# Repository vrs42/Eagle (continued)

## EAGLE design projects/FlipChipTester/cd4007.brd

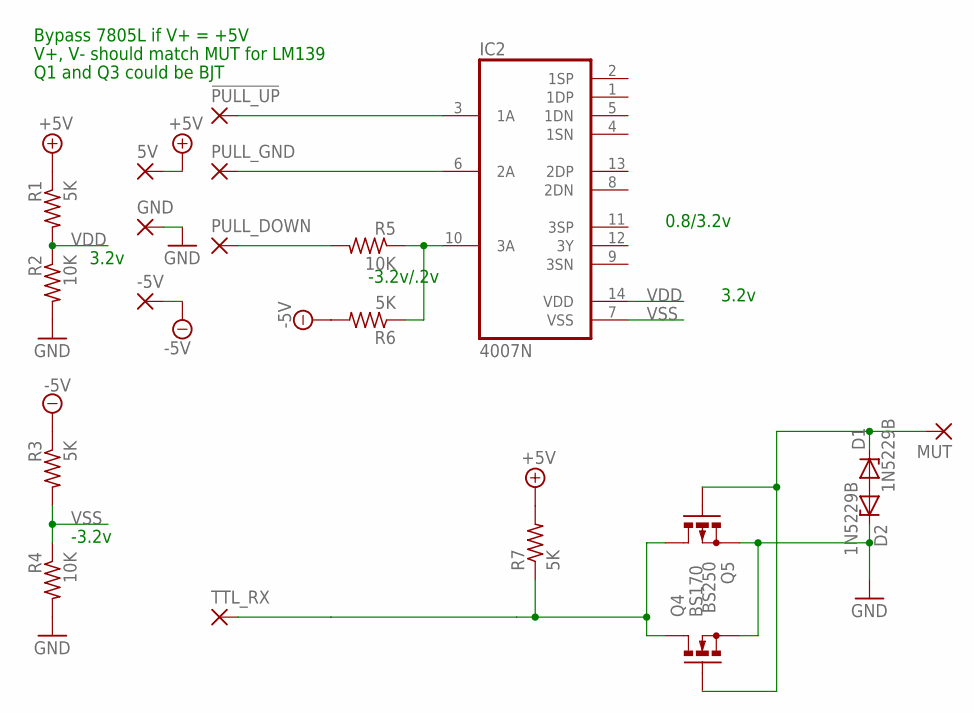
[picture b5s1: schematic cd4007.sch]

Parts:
5V: 1,6/0,9
!PULL_UP: 1,6/0,9
-5V: 1,6/0,9
D1, D2: 1N5229B; DO35Z10
GND: 1,6/0,9
IC2: 4007N; DIL14
MUT: 1,6/0,9
PULL_DOWN: 1,6/0,9
PULL_GND: 1,6/0,9
Q4: BS170; SOT54E
Q5: BS250; SOT54E
R1, R3, R6, R7: 5K; 0207/10
R2, R4, R5: 10K; 0207/10
TTL_RX: 1,6/0,9

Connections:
+5V: 5V.1, R1.1, R7.2
-5V: -5V.1, R3.1, R6.2
GND: D2.C, GND.1, Q4.S, Q5.S, R2.2, R4.2
unnamed: D1.C, MUT.1, Q4.G, Q5.G
unnamed: IC2.10 (3A), R5.1, R6.1
unnamed: IC2.6 (2A), PULL_GND.1
unnamed: PULL_DOWN.1, R5.2
unnamed: D1.A, D2.A
unnamed: Q4.D, Q5.D, R7.1, TTL_RX.1
unnamed: !PULL_UP.1, IC2.3 (1A)
VDD: IC2.14 (VDD), R1.2, R2.1
VSS: IC2.7 (VSS), R3.2, R4.1

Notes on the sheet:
V+, V- should match MUT for LM139
Bypass 7805L if V+ = +5V
-3.2v
-3.2v/.2v
3.2v
0.8/3.2v
Q1 and Q3 could be BJT

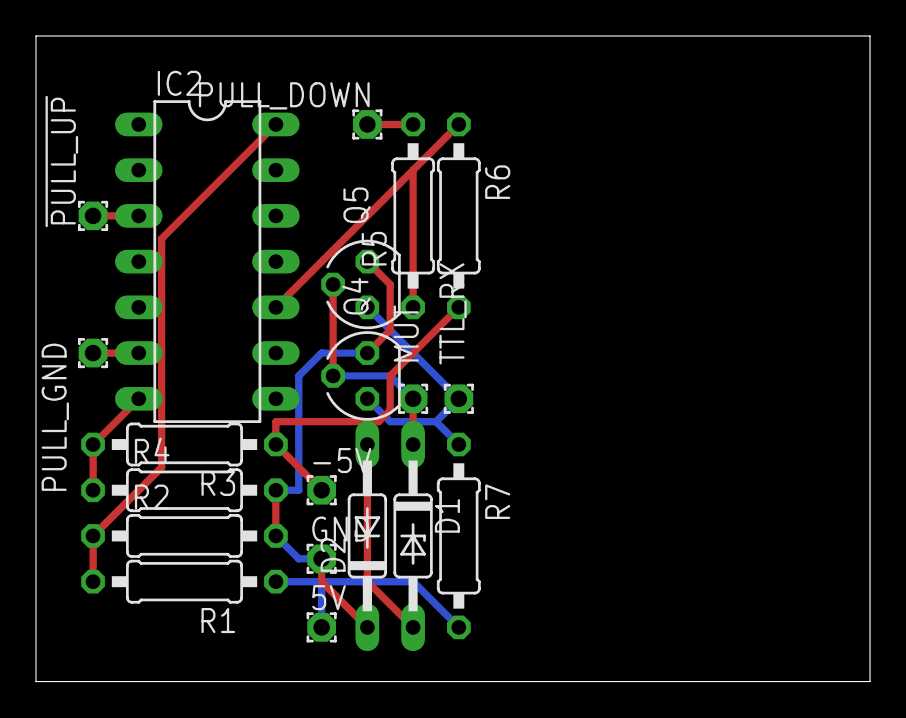
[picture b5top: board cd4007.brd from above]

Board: 2 copper layers, 46.3 x 35.9 mm, 20 parts (0 on the bottom side), 12 nets.

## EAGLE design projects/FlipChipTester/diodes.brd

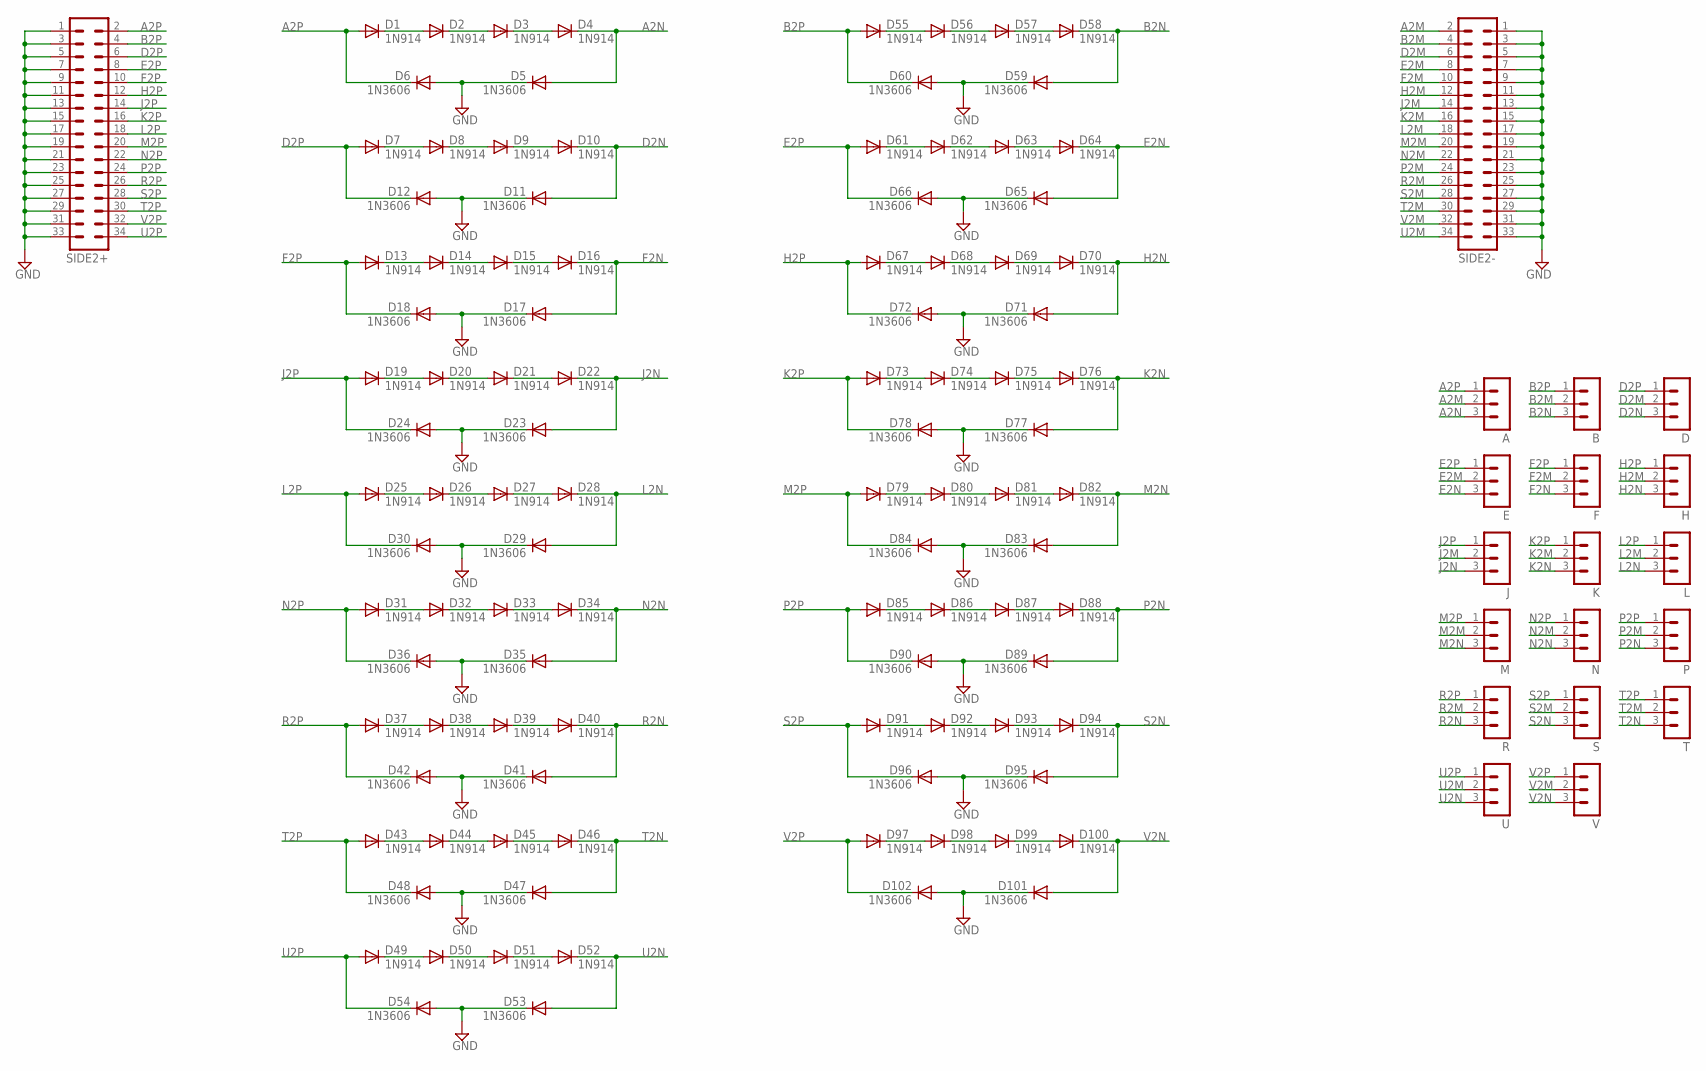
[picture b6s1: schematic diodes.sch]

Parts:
A: MA03-1
B: MA03-1
D: MA03-1
D1, D2, D3, D4, D7, D8, D9, D10, D13, D14, D15, D16, D19, D20, D21, D22, D25, D26, D27, D28, D31, D32, D33, D34, D37, D38, D39, D40, D43, D44, D45, D46, D49, D50, D51, D52, D55, D56, D57, D58, D61, D62, D63, D64, D67, D68, D69, D70, D73, D74, D75, D76, D79, D80, D81, D82, D85, D86, D87, D88, D91, D92, D93, D94, D97, D98, D99, D100: 1N914; DO35-10
D5, D6, D11, D12, D17, D18, D23, D24, D29, D30, D35, D36, D41, D42, D47, D48, D53, D54, D59, D60, D65, D66, D71, D72, D77, D78, D83, D84, D89, D90, D95, D96, D101, D102: 1N3606; DO35-10
E: MA03-1
F: MA03-1
H: MA03-1
J: MA03-1
K: MA03-1
L: MA03-1
M: MA03-1
N: MA03-1
P: MA03-1
R: MA03-1
S: MA03-1
SIDE2+, SIDE2-: MA17-2
T: MA03-1
U: MA03-1
V: MA03-1

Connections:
A2M: A.2, SIDE2-.2
A2N: A.3, D4.C, D5.A
A2P: A.1, D1.A, D6.C, SIDE2+.2
B2M: B.2, SIDE2-.4
B2N: B.3, D58.C, D59.A
B2P: B.1, D55.A, D60.C, SIDE2+.4
D2M: D.2, SIDE2-.6
D2N: D.3, D10.C, D11.A
D2P: D.1, D7.A, D12.C, SIDE2+.6
E2M: E.2, SIDE2-.8
E2N: D64.C, D65.A, E.3
E2P: D61.A, D66.C, E.1, SIDE2+.8
F2M: F.2, SIDE2-.10
F2N: D16.C, D17.A, F.3
F2P: D13.A, D18.C, F.1, SIDE2+.10
GND: D5.C, D6.A, D11.C, D12.A, D17.C, D18.A, D23.C, D24.A, D29.C, D30.A, D35.C, D36.A, D41.C, D42.A, D47.C, D48.A, D53.C, D54.A, D59.C, D60.A, D65.C, D66.A, D71.C, D72.A, D77.C, D78.A, D83.C, D84.A, D89.C, D90.A, D95.C, D96.A, D101.C, D102.A, SIDE2+.1, SIDE2+.3, SIDE2+.5, SIDE2+.7, SIDE2+.9, SIDE2+.11, SIDE2+.13, SIDE2+.15, SIDE2+.17, SIDE2+.19, SIDE2+.21, SIDE2+.23, SIDE2+.25, SIDE2+.27, SIDE2+.29, SIDE2+.31, SIDE2+.33, SIDE2-.1, SIDE2-.3, SIDE2-.5, SIDE2-.7, SIDE2-.9, SIDE2-.11, SIDE2-.13, SIDE2-.15, SIDE2-.17, SIDE2-.19, SIDE2-.21, SIDE2-.23, SIDE2-.25, SIDE2-.27, SIDE2-.29, SIDE2-.31, SIDE2-.33
H2M: H.2, SIDE2-.12
H2N: D70.C, D71.A, H.3
H2P: D67.A, D72.C, H.1, SIDE2+.12
J2M: J.2, SIDE2-.14
J2N: D22.C, D23.A, J.3
J2P: D19.A, D24.C, J.1, SIDE2+.14
K2M: K.2, SIDE2-.16
K2N: D76.C, D77.A, K.3
K2P: D73.A, D78.C, K.1, SIDE2+.16
L2M: L.2, SIDE2-.18
L2N: D28.C, D29.A, L.3
L2P: D25.A, D30.C, L.1, SIDE2+.18
M2M: M.2, SIDE2-.20
M2N: D82.C, D83.A, M.3
M2P: D79.A, D84.C, M.1, SIDE2+.20
N2M: N.2, SIDE2-.22
N2N: D34.C, D35.A, N.3
N2P: D31.A, D36.C, N.1, SIDE2+.22
unnamed: D1.C, D2.A
unnamed: D2.C, D3.A
unnamed: D3.C, D4.A
unnamed: D7.C, D8.A
unnamed: D8.C, D9.A
unnamed: D9.C, D10.A
unnamed: D13.C, D14.A
unnamed: D14.C, D15.A
unnamed: D15.C, D16.A
unnamed: D19.C, D20.A
unnamed: D20.C, D21.A
unnamed: D21.C, D22.A
unnamed: D25.C, D26.A
unnamed: D26.C, D27.A
unnamed: D27.C, D28.A
unnamed: D31.C, D32.A
unnamed: D32.C, D33.A
unnamed: D33.C, D34.A
unnamed: D37.C, D38.A
unnamed: D38.C, D39.A
unnamed: D39.C, D40.A
unnamed: D43.C, D44.A
unnamed: D44.C, D45.A
unnamed: D45.C, D46.A
unnamed: D49.C, D50.A
unnamed: D50.C, D51.A
unnamed: D51.C, D52.A
unnamed: D55.C, D56.A
unnamed: D56.C, D57.A
unnamed: D57.C, D58.A
unnamed: D61.C, D62.A
unnamed: D62.C, D63.A
unnamed: D63.C, D64.A
unnamed: D67.C, D68.A
unnamed: D68.C, D69.A
unnamed: D69.C, D70.A
unnamed: D73.C, D74.A
unnamed: D74.C, D75.A
unnamed: D75.C, D76.A
unnamed: D79.C, D80.A
unnamed: D80.C, D81.A
unnamed: D81.C, D82.A
unnamed: D85.C, D86.A
unnamed: D86.C, D87.A
unnamed: D87.C, D88.A
unnamed: D91.C, D92.A
unnamed: D92.C, D93.A
unnamed: D93.C, D94.A
unnamed: D97.C, D98.A
unnamed: D98.C, D99.A
unnamed: D99.C, D100.A
P2M: P.2, SIDE2-.24
P2N: D88.C, D89.A, P.3
P2P: D85.A, D90.C, P.1, SIDE2+.24
R2M: R.2, SIDE2-.26
R2N: D40.C, D41.A, R.3
R2P: D37.A, D42.C, R.1, SIDE2+.26
S2M: S.2, SIDE2-.28
S2N: D94.C, D95.A, S.3
S2P: D91.A, D96.C, S.1, SIDE2+.28
T2M: SIDE2-.30, T.2
T2N: D46.C, D47.A, T.3
T2P: D43.A, D48.C, SIDE2+.30, T.1
U2M: SIDE2-.34, U.2
U2N: D52.C, D53.A, U.3
U2P: D49.A, D54.C, SIDE2+.34, U.1
V2M: SIDE2-.32, V.2
V2N: D100.C, D101.A, V.3
V2P: D97.A, D102.C, SIDE2+.32, V.1

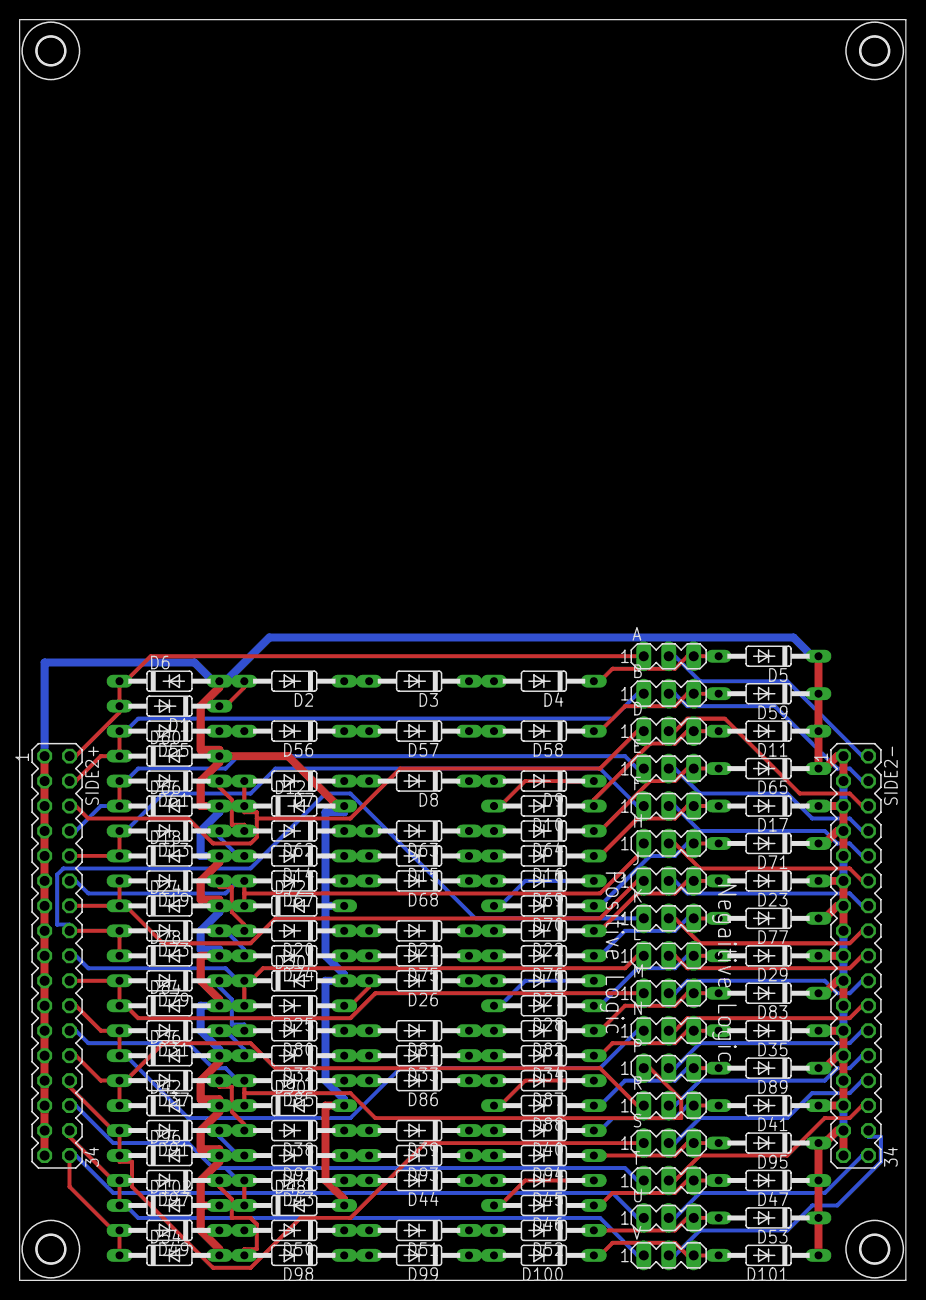
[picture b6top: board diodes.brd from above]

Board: 2 copper layers, 90.2 x 128.3 mm, 125 parts (0 on the bottom side), 103 nets.

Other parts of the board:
U$1, U$2, U$3, U$4: 2,8

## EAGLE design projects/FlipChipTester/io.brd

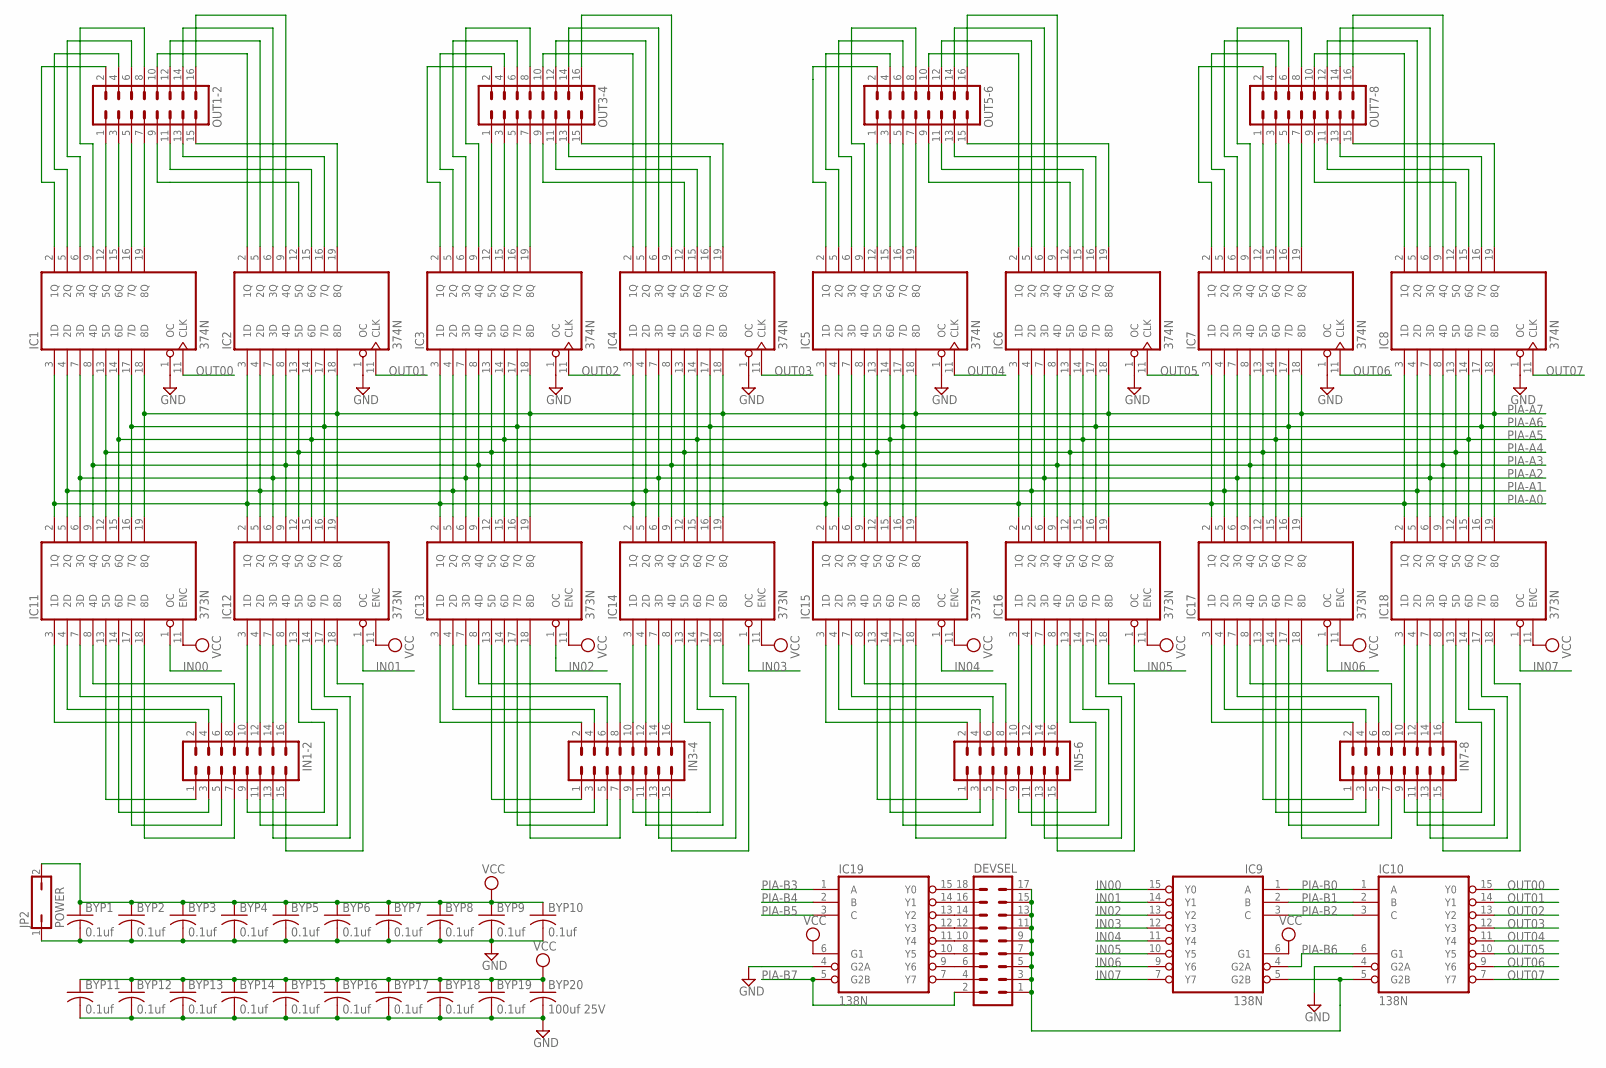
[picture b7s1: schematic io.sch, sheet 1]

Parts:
BYP1, BYP2, BYP3, BYP4, BYP5, BYP6, BYP7, BYP8, BYP9, BYP10, BYP11, BYP12, BYP13, BYP14, BYP15, BYP16, BYP17, BYP18, BYP19: 0.1uf; C050-025X075
BYP20: 100uf 25V; C150-064X183
DEVSEL: MA09-2
IC1, IC2, IC3, IC4, IC5, IC6, IC7, IC8: 374N; DIL20
IC9, IC10, IC19: 138N; DIL16
IC11, IC12, IC13, IC14, IC15, IC16, IC17, IC18: 373N; DIL20
IN1-2, IN3-4, IN5-6, IN7-8: MA08-2
JP2: POWER; JP1
OUT1-2, OUT3-4, OUT5-6, OUT7-8: MA08-2

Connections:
GND: BYP1.2, BYP2.2, BYP3.2, BYP4.2, BYP5.2, BYP6.2, BYP7.2, BYP8.2, BYP9.2, BYP10.2, BYP11.2, BYP12.2, BYP13.2, BYP14.2, BYP15.2, BYP16.2, BYP17.2, BYP18.2, BYP19.2, BYP20.2, IC1.1 (OC), IC1.10 (GND), IC2.1 (OC), IC2.10 (GND), IC3.1 (OC), IC3.10 (GND), IC4.1 (OC), IC4.10 (GND), IC5.1 (OC), IC5.10 (GND), IC6.1 (OC), IC6.10 (GND), IC7.1 (OC), IC7.10 (GND), IC8.1 (OC), IC8.10 (GND), IC9.8 (GND), IC10.4 (G2A), IC10.8 (GND), IC11.10 (GND), IC12.10 (GND), IC13.10 (GND), IC14.10 (GND), IC15.10 (GND), IC16.10 (GND), IC17.10 (GND), IC18.10 (GND), IC19.4 (G2A), IC19.8 (GND), JP2.1; also elsewhere on the board
IN00: IC9.15 (Y0), IC11.1 (OC)
IN01: IC9.14 (Y1), IC12.1 (OC)
IN02: IC9.13 (Y2), IC13.1 (OC)
IN03: IC9.12 (Y3), IC14.1 (OC)
IN04: IC9.11 (Y4), IC15.1 (OC)
IN05: IC9.10 (Y5), IC16.1 (OC)
IN06: IC9.9 (Y6), IC17.1 (OC)
IN07: IC9.7 (Y7), IC18.1 (OC)
unnamed: IC12.3 (1D), IN1-2.10
unnamed: IC12.4 (2D), IN1-2.12
unnamed: DEVSEL.18, IC19.15 (Y0)
unnamed: DEVSEL.16, IC19.14 (Y1)
unnamed: DEVSEL.14, IC19.13 (Y2)
unnamed: DEVSEL.12, IC19.12 (Y3)
unnamed: IC12.7 (3D), IN1-2.14
unnamed: IC12.8 (4D), IN1-2.16
unnamed: IC11.8 (4D), IN1-2.8
unnamed: IC11.7 (3D), IN1-2.6
unnamed: IC11.4 (2D), IN1-2.4
unnamed: IC11.3 (1D), IN1-2.2
unnamed: IC11.13 (5D), IN1-2.1
unnamed: IC11.14 (6D), IN1-2.3
unnamed: IC11.17 (7D), IN1-2.5
unnamed: IC11.18 (8D), IN1-2.7
unnamed: IC12.13 (5D), IN1-2.9
unnamed: IC12.14 (6D), IN1-2.11
unnamed: IC12.17 (7D), IN1-2.13
unnamed: IC12.18 (8D), IN1-2.15
unnamed: DEVSEL.10, IC19.11 (Y4)
unnamed: DEVSEL.8, IC19.10 (Y5)
unnamed: DEVSEL.6, IC19.9 (Y6)
unnamed: DEVSEL.4, IC19.7 (Y7)
unnamed: DEVSEL.1, DEVSEL.3, DEVSEL.5, DEVSEL.7, DEVSEL.9, DEVSEL.11, DEVSEL.13, DEVSEL.15, DEVSEL.17, IC9.5 (G2B), IC10.5 (G2B)
unnamed: IC5.2 (1Q), OUT5-6.2
unnamed: IC18.8 (4D), IN7-8.16
unnamed: IC18.3 (1D), IN7-8.10
unnamed: IC14.3 (1D), IN3-4.10
unnamed: IC14.4 (2D), IN3-4.12
unnamed: IC14.7 (3D), IN3-4.14
unnamed: IC14.8 (4D), IN3-4.16
unnamed: IC3.12 (5Q), OUT3-4.1
unnamed: IC3.15 (6Q), OUT3-4.3
unnamed: IC3.16 (7Q), OUT3-4.5
unnamed: IC3.19 (8Q), OUT3-4.7
unnamed: IC13.3 (1D), IN3-4.2
unnamed: IC13.4 (2D), IN3-4.4
unnamed: IC13.7 (3D), IN3-4.6
unnamed: IC13.8 (4D), IN3-4.8
unnamed: IC14.13 (5D), IN3-4.9
unnamed: IC14.14 (6D), IN3-4.11
unnamed: IC14.17 (7D), IN3-4.13
unnamed: IC14.18 (8D), IN3-4.15
unnamed: IC13.13 (5D), IN3-4.1
unnamed: IC13.14 (6D), IN3-4.3
unnamed: IC13.17 (7D), IN3-4.5
unnamed: IC13.18 (8D), IN3-4.7
unnamed: IC3.5 (2Q), OUT3-4.4
unnamed: IC3.6 (3Q), OUT3-4.6
unnamed: IC3.2 (1Q), OUT3-4.2
unnamed: IC3.9 (4Q), OUT3-4.8
unnamed: IC1.12 (5Q), OUT1-2.1
unnamed: IC1.15 (6Q), OUT1-2.3
unnamed: IC1.16 (7Q), OUT1-2.5
unnamed: IC1.19 (8Q), OUT1-2.7
unnamed: IC1.2 (1Q), OUT1-2.2
unnamed: IC1.5 (2Q), OUT1-2.4
unnamed: IC1.6 (3Q), OUT1-2.6
unnamed: IC1.9 (4Q), OUT1-2.8
unnamed: IC2.19 (8Q), OUT1-2.15
unnamed: IC2.16 (7Q), OUT1-2.13
unnamed: IC2.15 (6Q), OUT1-2.11
unnamed: IC2.12 (5Q), OUT1-2.9
unnamed: IC2.2 (1Q), OUT1-2.10
unnamed: IC2.5 (2Q), OUT1-2.12
unnamed: IC2.6 (3Q), OUT1-2.14
unnamed: IC2.9 (4Q), OUT1-2.16
unnamed: IC4.2 (1Q), OUT3-4.10
unnamed: IC4.5 (2Q), OUT3-4.12
unnamed: IC4.6 (3Q), OUT3-4.14
unnamed: IC4.9 (4Q), OUT3-4.16
unnamed: IC4.19 (8Q), OUT3-4.15
unnamed: IC4.16 (7Q), OUT3-4.13
unnamed: IC4.15 (6Q), OUT3-4.11
unnamed: IC4.12 (5Q), OUT3-4.9
unnamed: IC16.3 (1D), IN5-6.10
unnamed: IC16.4 (2D), IN5-6.12
unnamed: IC16.7 (3D), IN5-6.14
unnamed: IC16.8 (4D), IN5-6.16
unnamed: IC5.12 (5Q), OUT5-6.1
unnamed: IC5.15 (6Q), OUT5-6.3
unnamed: IC5.16 (7Q), OUT5-6.5
unnamed: IC5.19 (8Q), OUT5-6.7
unnamed: IC7.12 (5Q), OUT7-8.1
unnamed: IC7.15 (6Q), OUT7-8.3
unnamed: IC7.16 (7Q), OUT7-8.5
unnamed: IC7.19 (8Q), OUT7-8.7
unnamed: IC5.5 (2Q), OUT5-6.4
unnamed: IC5.6 (3Q), OUT5-6.6
unnamed: IC5.9 (4Q), OUT5-6.8
unnamed: IC6.12 (5Q), OUT5-6.9
unnamed: IC6.15 (6Q), OUT5-6.11
unnamed: IC18.4 (2D), IN7-8.12
unnamed: IC6.16 (7Q), OUT5-6.13
unnamed: IC6.19 (8Q), OUT5-6.15
unnamed: IC6.2 (1Q), OUT5-6.10
unnamed: IC6.5 (2Q), OUT5-6.12
unnamed: IC6.6 (3Q), OUT5-6.14
unnamed: IC6.9 (4Q), OUT5-6.16
unnamed: IC15.3 (1D), IN5-6.2
unnamed: IC15.4 (2D), IN5-6.4
unnamed: IC15.7 (3D), IN5-6.6
unnamed: IC15.8 (4D), IN5-6.8
unnamed: IC16.13 (5D), IN5-6.9
unnamed: IC16.14 (6D), IN5-6.11
unnamed: IC16.17 (7D), IN5-6.13
unnamed: IC16.18 (8D), IN5-6.15
unnamed: IC15.13 (5D), IN5-6.1
unnamed: IC15.14 (6D), IN5-6.3
unnamed: IC15.17 (7D), IN5-6.5
unnamed: IC15.18 (8D), IN5-6.7
unnamed: IC8.19 (8Q), OUT7-8.15
unnamed: IC8.16 (7Q), OUT7-8.13
unnamed: IC8.15 (6Q), OUT7-8.11
unnamed: IC8.12 (5Q), OUT7-8.9
unnamed: IC8.2 (1Q), OUT7-8.10
unnamed: IC8.5 (2Q), OUT7-8.12
unnamed: IC8.6 (3Q), OUT7-8.14
unnamed: IC8.9 (4Q), OUT7-8.16
unnamed: IC7.9 (4Q), OUT7-8.8
unnamed: IC7.6 (3Q), OUT7-8.6
unnamed: IC7.5 (2Q), OUT7-8.4
unnamed: IC18.7 (3D), IN7-8.14
unnamed: IC18.13 (5D), IN7-8.9
unnamed: IC18.14 (6D), IN7-8.11
unnamed: IC18.17 (7D), IN7-8.13
unnamed: IC18.18 (8D), IN7-8.15
unnamed: IC17.3 (1D), IN7-8.2
unnamed: IC17.4 (2D), IN7-8.4
unnamed: IC17.7 (3D), IN7-8.6
unnamed: IC17.8 (4D), IN7-8.8
unnamed: IC17.13 (5D), IN7-8.1
unnamed: IC17.14 (6D), IN7-8.3
unnamed: IC17.17 (7D), IN7-8.5
unnamed: IC17.18 (8D), IN7-8.7
unnamed: IC7.2 (1Q), OUT7-8.2
OUT00: IC1.11 (CLK), IC10.15 (Y0)
OUT01: IC2.11 (CLK), IC10.14 (Y1)
OUT02: IC3.11 (CLK), IC10.13 (Y2)
OUT03: IC4.11 (CLK), IC10.12 (Y3)
OUT04: IC5.11 (CLK), IC10.11 (Y4)
OUT05: IC6.11 (CLK), IC10.10 (Y5)
OUT06: IC7.11 (CLK), IC10.9 (Y6)
OUT07: IC8.11 (CLK), IC10.7 (Y7)
PIA-A0: IC1.3 (1D), IC2.3 (1D), IC3.3 (1D), IC4.3 (1D), IC5.3 (1D), IC6.3 (1D), IC7.3 (1D), IC8.3 (1D), IC11.2 (1Q), IC12.2 (1Q), IC13.2 (1Q), IC14.2 (1Q), IC15.2 (1Q), IC16.2 (1Q), IC17.2 (1Q), IC18.2 (1Q); also elsewhere on the board
PIA-A1: IC1.4 (2D), IC2.4 (2D), IC3.4 (2D), IC4.4 (2D), IC5.4 (2D), IC6.4 (2D), IC7.4 (2D), IC8.4 (2D), IC11.5 (2Q), IC12.5 (2Q), IC13.5 (2Q), IC14.5 (2Q), IC15.5 (2Q), IC16.5 (2Q), IC17.5 (2Q), IC18.5 (2Q); also elsewhere on the board
PIA-A2: IC1.7 (3D), IC2.7 (3D), IC3.7 (3D), IC4.7 (3D), IC5.7 (3D), IC6.7 (3D), IC7.7 (3D), IC8.7 (3D), IC11.6 (3Q), IC12.6 (3Q), IC13.6 (3Q), IC14.6 (3Q), IC15.6 (3Q), IC16.6 (3Q), IC17.6 (3Q), IC18.6 (3Q); also elsewhere on the board
PIA-A3: IC1.8 (4D), IC2.8 (4D), IC3.8 (4D), IC4.8 (4D), IC5.8 (4D), IC6.8 (4D), IC7.8 (4D), IC8.8 (4D), IC11.9 (4Q), IC12.9 (4Q), IC13.9 (4Q), IC14.9 (4Q), IC15.9 (4Q), IC16.9 (4Q), IC17.9 (4Q), IC18.9 (4Q); also elsewhere on the board
PIA-A4: IC1.13 (5D), IC2.13 (5D), IC3.13 (5D), IC4.13 (5D), IC5.13 (5D), IC6.13 (5D), IC7.13 (5D), IC8.13 (5D), IC11.12 (5Q), IC12.12 (5Q), IC13.12 (5Q), IC14.12 (5Q), IC15.12 (5Q), IC16.12 (5Q), IC17.12 (5Q), IC18.12 (5Q); also elsewhere on the board
PIA-A5: IC1.14 (6D), IC2.14 (6D), IC3.14 (6D), IC4.14 (6D), IC5.14 (6D), IC6.14 (6D), IC7.14 (6D), IC8.14 (6D), IC11.15 (6Q), IC12.15 (6Q), IC13.15 (6Q), IC14.15 (6Q), IC15.15 (6Q), IC16.15 (6Q), IC17.15 (6Q), IC18.15 (6Q); also elsewhere on the board
PIA-A6: IC1.17 (7D), IC2.17 (7D), IC3.17 (7D), IC4.17 (7D), IC5.17 (7D), IC6.17 (7D), IC7.17 (7D), IC8.17 (7D), IC11.16 (7Q), IC12.16 (7Q), IC13.16 (7Q), IC14.16 (7Q), IC15.16 (7Q), IC16.16 (7Q), IC17.16 (7Q), IC18.16 (7Q); also elsewhere on the board
PIA-A7: IC1.18 (8D), IC2.18 (8D), IC3.18 (8D), IC4.18 (8D), IC5.18 (8D), IC6.18 (8D), IC7.18 (8D), IC8.18 (8D), IC11.19 (8Q), IC12.19 (8Q), IC13.19 (8Q), IC14.19 (8Q), IC15.19 (8Q), IC16.19 (8Q), IC17.19 (8Q), IC18.19 (8Q); also elsewhere on the board
PIA-B0: IC9.1 (A), IC10.1 (A); also elsewhere on the board
PIA-B1: IC9.2 (B), IC10.2 (B); also elsewhere on the board
PIA-B2: IC9.3 (C), IC10.3 (C); also elsewhere on the board
PIA-B3: IC19.1 (A); also elsewhere on the board
PIA-B4: IC19.2 (B); also elsewhere on the board
PIA-B5: IC19.3 (C); also elsewhere on the board
PIA-B6: IC9.4 (G2A), IC10.6 (G1); also elsewhere on the board
PIA-B7: DEVSEL.2, IC19.5 (G2B); also elsewhere on the board
VCC: BYP1.1, BYP2.1, BYP3.1, BYP4.1, BYP5.1, BYP6.1, BYP7.1, BYP8.1, BYP9.1, BYP10.1, BYP11.1, BYP12.1, BYP13.1, BYP14.1, BYP15.1, BYP16.1, BYP17.1, BYP18.1, BYP19.1, BYP20.1, IC1.20 (VCC), IC2.20 (VCC), IC3.20 (VCC), IC4.20 (VCC), IC5.20 (VCC), IC6.20 (VCC), IC7.20 (VCC), IC8.20 (VCC), IC9.6 (G1), IC9.16 (VCC), IC10.16 (VCC), IC11.11 (ENC), IC11.20 (VCC), IC12.11 (ENC), IC12.20 (VCC), IC13.11 (ENC), IC13.20 (VCC), IC14.11 (ENC), IC14.20 (VCC), IC15.11 (ENC), IC15.20 (VCC), IC16.11 (ENC), IC16.20 (VCC), IC17.11 (ENC), IC17.20 (VCC), IC18.11 (ENC), IC18.20 (VCC), IC19.6 (G1), IC19.16 (VCC), JP2.2; also elsewhere on the board

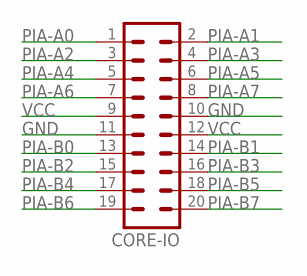
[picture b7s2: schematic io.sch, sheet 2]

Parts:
CORE-IO: MA10-2

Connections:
GND: CORE-IO.10, CORE-IO.11; also elsewhere on the board
PIA-A0: CORE-IO.1; also elsewhere on the board
PIA-A1: CORE-IO.2; also elsewhere on the board
PIA-A2: CORE-IO.3; also elsewhere on the board
PIA-A3: CORE-IO.4; also elsewhere on the board
PIA-A4: CORE-IO.5; also elsewhere on the board
PIA-A5: CORE-IO.6; also elsewhere on the board
PIA-A6: CORE-IO.7; also elsewhere on the board
PIA-A7: CORE-IO.8; also elsewhere on the board
PIA-B0: CORE-IO.13; also elsewhere on the board
PIA-B1: CORE-IO.14; also elsewhere on the board
PIA-B2: CORE-IO.15; also elsewhere on the board
PIA-B3: CORE-IO.16; also elsewhere on the board
PIA-B4: CORE-IO.17; also elsewhere on the board
PIA-B5: CORE-IO.18; also elsewhere on the board
PIA-B6: CORE-IO.19; also elsewhere on the board
PIA-B7: CORE-IO.20; also elsewhere on the board
VCC: CORE-IO.9, CORE-IO.12; also elsewhere on the board

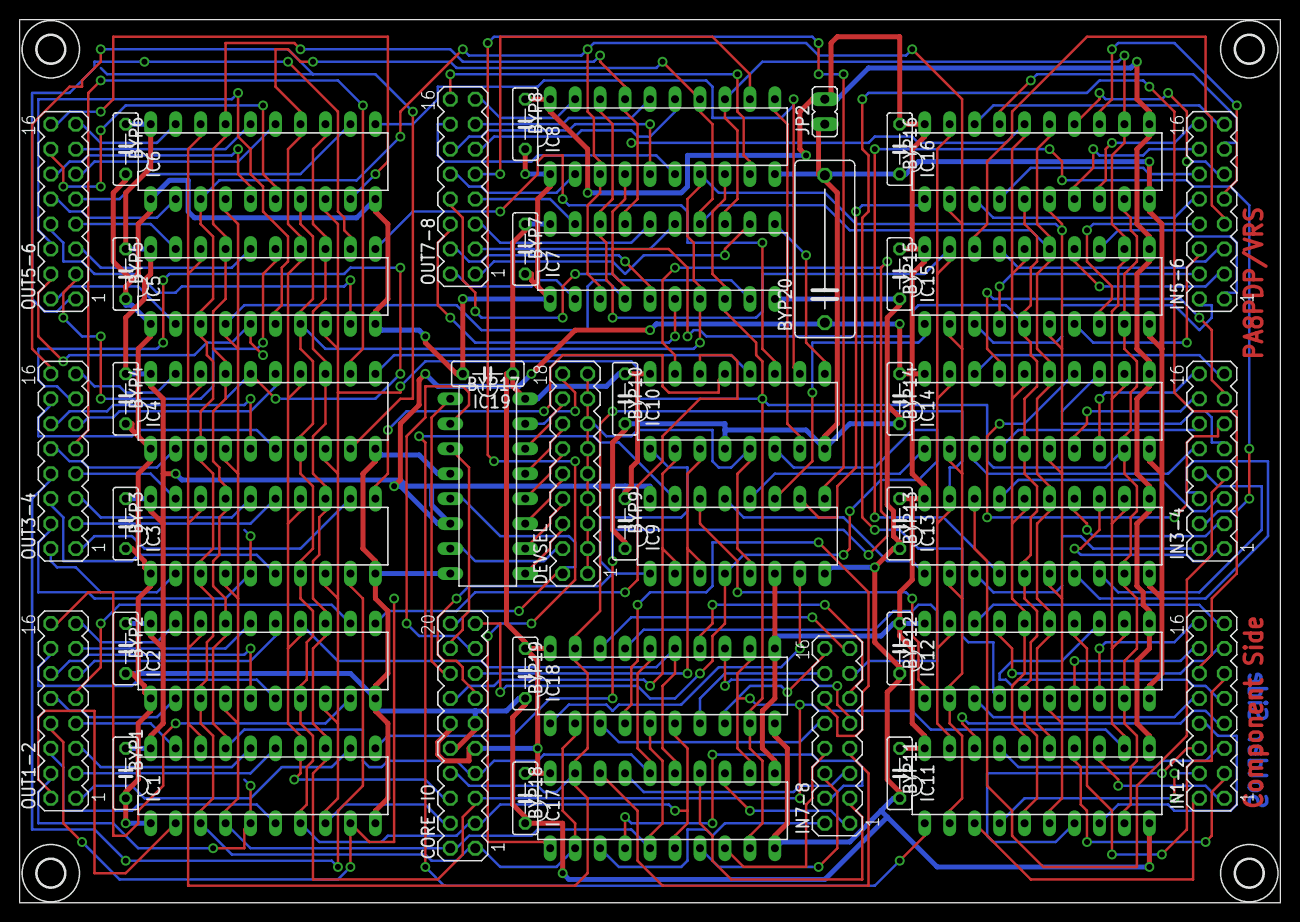
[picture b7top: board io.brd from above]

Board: 2 copper layers, 128.2 x 89.8 mm, 54 parts (0 on the bottom side), 171 nets.

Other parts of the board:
U$1, U$2, U$3, U$4: 2,8
